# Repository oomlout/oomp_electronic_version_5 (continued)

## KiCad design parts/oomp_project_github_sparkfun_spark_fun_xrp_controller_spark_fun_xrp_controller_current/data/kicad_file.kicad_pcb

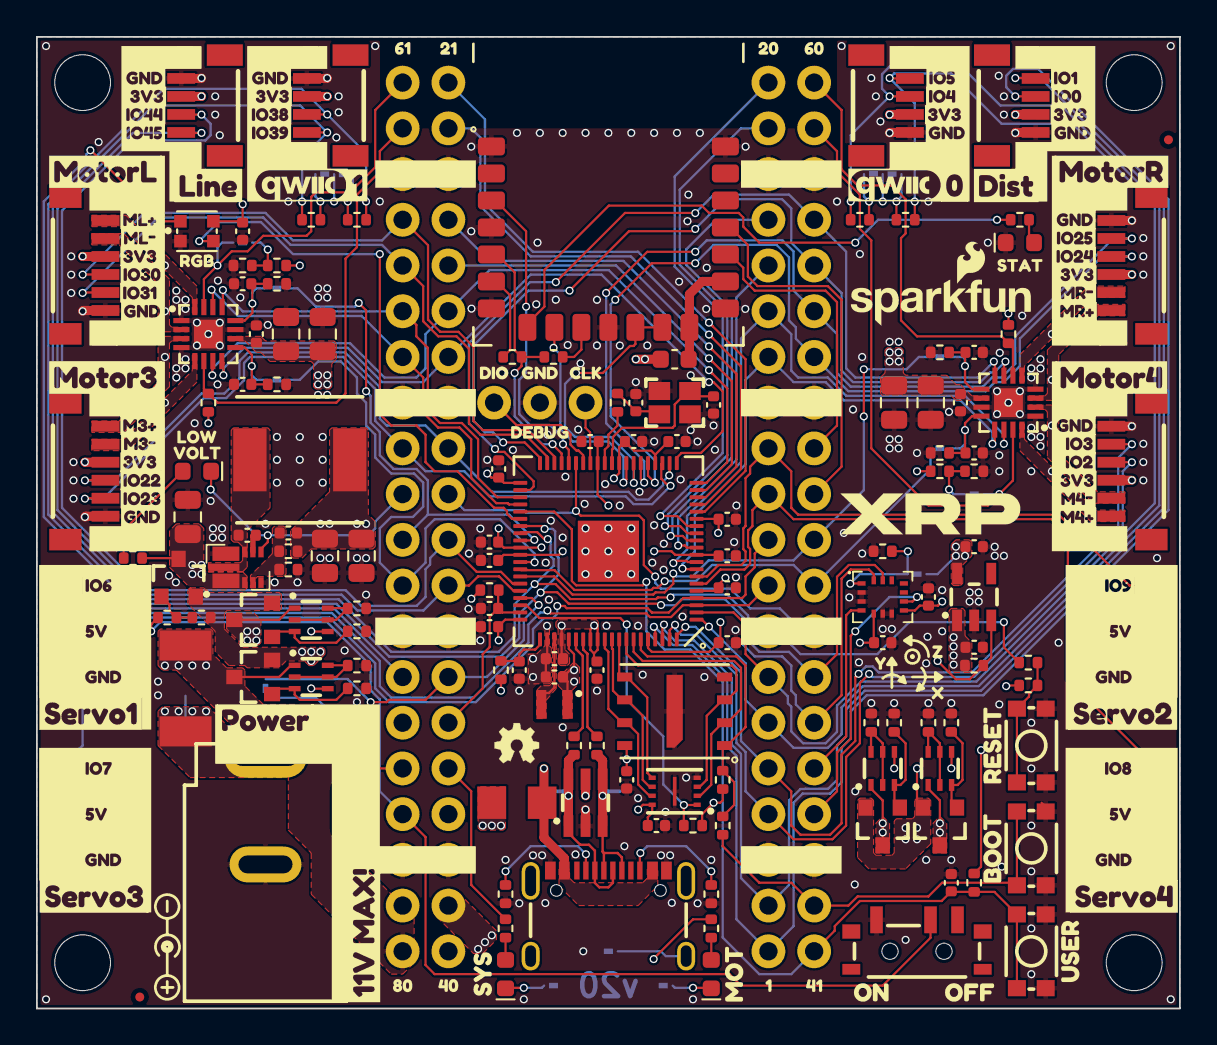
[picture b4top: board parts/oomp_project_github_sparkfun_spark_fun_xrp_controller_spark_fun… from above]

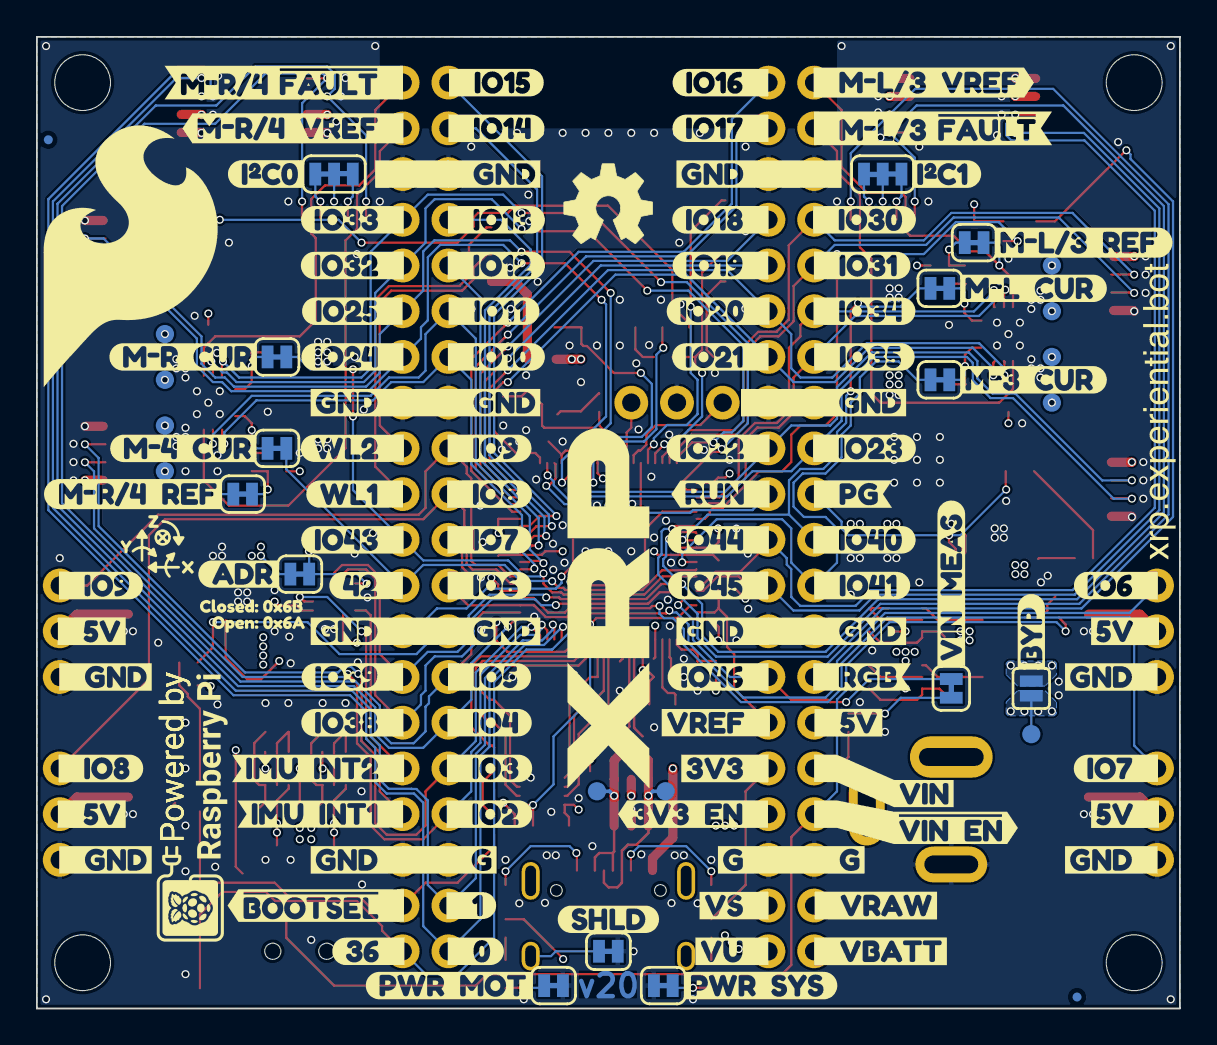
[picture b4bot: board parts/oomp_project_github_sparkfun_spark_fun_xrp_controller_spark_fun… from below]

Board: 6 copper layers, 63.5 x 54.0 mm, 385 parts (137 on the bottom side), 137 nets.

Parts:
C1, C2, C3, C4, C5, C6, C7, C8, C9, C10, C11, C19, C20, C22, C28, C29, C30, C31, C34, C37, C42, C43, C44, C45: 0.1uF; C_0402_1005Metric
C12, C13, C14, C15, C16, C26, C27: 4.7uF; C_0402_1005Metric
C17, C18: 15pF; C_0402_1005Metric
C21, C24, C25, C32, C33, C35, C36, C38, C39, C40, C41: 22uF; C_0805_2012Metric
C23: 47pF; C_0402_1005Metric
D1: Blue; LED_0603_1608Metric_Blue
D2, D3, D6: Red; LED_0603_1608Metric_Red
D4: WS2812B; WS2812_2020
D5: DT1042-04SO; SOT23-6
F1: 16V/2.5A/5.0A; 1812
F2: 6V/0.75A/1.5A; 1206
FID1, FID2, FID3, FID4: Fiducial_0.5mm; Fiducial_0.5mm_Mask1mm
G3: OSHW_Logo; Creative_Commons_License
J1: Barrel_Jack_PTH_Slot; Power_Jack_PTH_Slot
J2: USB_C_Receptacle; USB-C_16
J3, J8, J9, J10, J11: Conn_01x03; 1x03
J4, J5, J6, J7: Conn_01x20; 1x20
J12, J15: JST_SMD_1.0mm_Vertical; JST_SMD_1.0mm-4_Vertical
J13, J14: Qwiic_Vertical; JST_SMD_1.0mm-4_Vertical
J16, J17, J18, J19: Conn_01x06; JST_SMD_1.0mm-6_Vertical
JP1: PWR_SYS; Jumper_2_NC_Trace
JP2: PWR_MOT; Jumper_2_NC_Trace
JP3: BYP; Jumper_2_NO
JP4: ADR; Jumper_2_NC_Trace
JP5: I2C1; Jumper_3_NC-2_Trace
JP6: I2C0; Jumper_3_NC-2_Trace
JP7: SHLD; Jumper_2_NC_Trace
JP8: ML3_REF; Jumper_2_NC_Trace
JP9: MR4_REF; Jumper_2_NC_Trace
JP10: ML_CUR; Jumper_2_NC_Trace
JP11: M3_CUR; Jumper_2_NC_Trace
JP12: M4_CUR; Jumper_2_NC_Trace
JP13: MR_CUR; Jumper_2_NC_Trace
JP14: VIN_MEAS; Jumper_2_NC_Trace
L1: 3.3uH; 0806_Polarized
L2: 6.8uH; Inductor_7.3x6.6mm
L3: 470Ohm; C_0603_1608Metric
Q1, Q3, Q5, Q7: BCM857BS-7-F; SOT-323
Q2, Q4, Q6, Q8, Q9: DMG2305UX; SOT23-3
R1: 200; R_0402_1005Metric
R2: 33; R_0402_1005Metric
R3, R18, R20: 1k; R_0402_1005Metric
R4, R5: 27; R_0402_1005Metric
R6, R7, R12, R41: 10k; R_0402_1005Metric
R8: 180k; R_0402_1005Metric
R9, R23: 33k; R_0402_1005Metric
R10, R14, R15, R16, R17: 2.2k; R_0402_1005Metric
R11, R47: 4.7k; R_0402_1005Metric
R13, R19, R21, R22, R30, R31, R32, R33, R34, R35, R36, R37, R38, R39, R42, R43, R44, R45, R46, R48, R49: 100k; R_0402_1005Metric
R24, R25, R26, R27, R28, R29: 5.1k; R_0402_1005Metric
R40: 470; R_0402_1005Metric
Ref**: Val**; POLARITY_MARKING_CENTER_POSITIVE
Ref**#2: Val**; OSHW_Logo_2.5mm
Ref**#3: Val**; OSHW_Logo_5mm
ST1, ST2, ST3, ST4: Standoff
SW1: SPDT_Slide_SMD_6.7x2.6mm; Slide_SPST_SMD_6.7x2.6mm
SW2: RESET; Push_SMD_4.6x2.8mm_h2.5mm
SW3: BOOT; Push_SMD_4.6x2.8mm_h2.5mm
SW4: USER; Push_SMD_4.6x2.8mm_h2.5mm
TP1, TP2, TP4, TP5, TP6, TP7, TP8, TP9, TP10, TP11, TP12: 1.0mm; TestPoint-1.0mm
U1: RP2350B; QFN-80-1EP_10x10mm_P0.4mm_EP3.4x3.4mm
U2: W25Q128JVPIM; WDFN-8_6x5mm-SkinnyCenterPad
U3: APS6404L-3SQR-ZR; USON-8_3x2mm-SkinnyCenterPad
U4: AP63357DV-7; PowerVFDFN-13
U5: RT9080-3.3; SOT23-5
U6: LSM6DSOX; LGA-14L
U7, U8: DRV8411A; QFN-16
U9: RM2; RM2_Tight
Y1: 12MHz; Crystal_SMD_2.5x2.0mm
kibuzzard-66C8BA89: G***; kibuzzard-66C8BA89
kibuzzard-66C8BABD: G***; kibuzzard-66C8BABD
kibuzzard-66C8BAD7: G***; kibuzzard-66C8BAD7
kibuzzard-66C8BAE0: G***; kibuzzard-66C8BAE0
kibuzzard-66C8BAF9: G***; kibuzzard-66C8BAF9
kibuzzard-66C8BB00: G***; kibuzzard-66C8BB00
kibuzzard-66C8BB0B: G***; kibuzzard-66C8BB0B
kibuzzard-66C8BB07: G***; kibuzzard-66C8BB07
kibuzzard-66C8BB11: G***; kibuzzard-66C8BB11
kibuzzard-66C8BB15: G***; kibuzzard-66C8BB15
kibuzzard-66C8BB40: G***; kibuzzard-66C8BB40
kibuzzard-66C8BC20, kibuzzard-66C8BC20#2, kibuzzard-66C8BC20#3, kibuzzard-66C8BC20#4, kibuzzard-66C8BC20#5, kibuzzard-66C8BC20#6, kibuzzard-66C8BC20#7, kibuzzard-66C8BC20#8, kibuzzard-66C8BC20#9, kibuzzard-66C8BC20#10, kibuzzard-66C8BC20#11, kibuzzard-66C8BC20#12: G***; kibuzzard-66C8BC20
kibuzzard-66C8BCAF: G***; kibuzzard-66C8BCAF
kibuzzard-66C8BCB7: G***; kibuzzard-66C8BCB7
kibuzzard-66C8BCBF, kibuzzard-66C8BCBF#2, kibuzzard-66C8BCBF#3, kibuzzard-66C8BCBF#4, kibuzzard-66C8BCBF#5, kibuzzard-66C8BCBF#6, kibuzzard-66C8BCBF#7, kibuzzard-66C8BCBF#8: G***; kibuzzard-66C8BCBF
kibuzzard-66C8BCC4: G***; kibuzzard-66C8BCC4
kibuzzard-66C8BCCB: G***; kibuzzard-66C8BCCB
kibuzzard-66C8BD65, kibuzzard-66C8BD65#2, kibuzzard-66C8BD65#3, kibuzzard-66C8BD65#4: G***; kibuzzard-66C8BD65
kibuzzard-66C8C0A3: G***; kibuzzard-66C8C0A3
kibuzzard-66C8C0B9: G***; kibuzzard-66C8C0B9
kibuzzard-66C8C028: G***; kibuzzard-66C8C028
kibuzzard-66C8C031: G***; kibuzzard-66C8C031
kibuzzard-66D0C3E9: G***; kibuzzard-66D0C3E9
kibuzzard-66D0C3F4: G***; kibuzzard-66D0C3F4
kibuzzard-66D0F23E: G***; kibuzzard-66D0F23E
kibuzzard-675A0A02: G***; kibuzzard-675A0A02
kibuzzard-675A0A2C: G***; kibuzzard-675A0A2C
kibuzzard-675A0A3A: G***; kibuzzard-675A0A3A
kibuzzard-675A0A4A: G***; kibuzzard-675A0A4A
kibuzzard-675A0A6A: G***; kibuzzard-675A0A6A
kibuzzard-675A0A8E: G***; kibuzzard-675A0A8E
kibuzzard-675A0A9F: G***; kibuzzard-675A0A9F
kibuzzard-675A0A13: G***; kibuzzard-675A0A13
kibuzzard-675A0A24: G***; kibuzzard-675A0A24
kibuzzard-675A0A32: G***; kibuzzard-675A0A32
kibuzzard-675A0A42: G***; kibuzzard-675A0A42
kibuzzard-675A0A51: G***; kibuzzard-675A0A51
kibuzzard-675A0A59: G***; kibuzzard-675A0A59
kibuzzard-675A0A60: G***; kibuzzard-675A0A60
kibuzzard-675A0A71: G***; kibuzzard-675A0A71
kibuzzard-675A0A79: G***; kibuzzard-675A0A79
kibuzzard-675A0A84: G***; kibuzzard-675A0A84
kibuzzard-675A0AA6: G***; kibuzzard-675A0AA6
kibuzzard-675A0B2A: G***; kibuzzard-675A0B2A
kibuzzard-675A0B4B: G***; kibuzzard-675A0B4B
kibuzzard-675A0B42: G***; kibuzzard-675A0B42
kibuzzard-675A0C02: G***; kibuzzard-675A0C02
kibuzzard-675A0C47: G***; kibuzzard-675A0C47
kibuzzard-675A0C69: G***; kibuzzard-675A0C69
kibuzzard-675A0C74: G***; kibuzzard-675A0C74
kibuzzard-675A0CA1: G***; kibuzzard-675A0CA1
kibuzzard-675A07AD: G***; kibuzzard-675A07AD
kibuzzard-675A07C3: G***; kibuzzard-675A07C3
kibuzzard-675A07CE: G***; kibuzzard-675A07CE
kibuzzard-675A07D8: G***; kibuzzard-675A07D8
kibuzzard-675A07E1: G***; kibuzzard-675A07E1
kibuzzard-675A08A3: G***; kibuzzard-675A08A3
kibuzzard-675A08AB: G***; kibuzzard-675A08AB
kibuzzard-675A08B3: G***; kibuzzard-675A08B3
kibuzzard-675A08BE: G***; kibuzzard-675A08BE
kibuzzard-675A08C5: G***; kibuzzard-675A08C5
kibuzzard-675A08CC: G***; kibuzzard-675A08CC
kibuzzard-675A08D1: G***; kibuzzard-675A08D1
kibuzzard-675A08D7: G***; kibuzzard-675A08D7
kibuzzard-675A08DD: G***; kibuzzard-675A08DD
kibuzzard-675A08E8: G***; kibuzzard-675A08E8
kibuzzard-675A08F4: G***; kibuzzard-675A08F4
kibuzzard-675A09A0: G***; kibuzzard-675A09A0
kibuzzard-675A09AB: G***; kibuzzard-675A09AB
kibuzzard-675A09C6: G***; kibuzzard-675A09C6
kibuzzard-675A09D0: G***; kibuzzard-675A09D0
kibuzzard-675A09E0: G***; kibuzzard-675A09E0
kibuzzard-675A09E8: G***; kibuzzard-675A09E8
kibuzzard-675A09F0: G***; kibuzzard-675A09F0
kibuzzard-675A09F8: G***; kibuzzard-675A09F8
kibuzzard-675A081C: G***; kibuzzard-675A081C
kibuzzard-675A082E: G***; kibuzzard-675A082E
kibuzzard-675A086F: G***; kibuzzard-675A086F
kibuzzard-675A089C: G***; kibuzzard-675A089C
kibuzzard-675A090C: G***; kibuzzard-675A090C
kibuzzard-675A094C: G***; kibuzzard-675A094C
kibuzzard-675A099A: G***; kibuzzard-675A099A
kibuzzard-675A0814: G***; kibuzzard-675A0814
kibuzzard-675A0838: G***; kibuzzard-675A0838
kibuzzard-675A0858: G***; kibuzzard-675A0858
kibuzzard-675A0863: G***; kibuzzard-675A0863
kibuzzard-675A0896: G***; kibuzzard-675A0896
kibuzzard-675A0913: G***; kibuzzard-675A0913
kibuzzard-675A0923: G***; kibuzzard-675A0923
kibuzzard-675A0928: G***; kibuzzard-675A0928
kibuzzard-675A0935: G***; kibuzzard-675A0935
kibuzzard-675A0944, kibuzzard-675A0944#2: G***; kibuzzard-675A0944
kibuzzard-675A0955: G***; kibuzzard-675A0955
kibuzzard-675A0971: G***; kibuzzard-675A0971
kibuzzard-675A0986: G***; kibuzzard-675A0986
kibuzzard-675B6FE7: G***; kibuzzard-675B6FE7
kibuzzard-675B6FED: G***; kibuzzard-675B6FED
kibuzzard-675B6FF7: G***; kibuzzard-675B6FF7
kibuzzard-675B6FFD: G***; kibuzzard-675B6FFD
kibuzzard-675B70E2: G***; kibuzzard-675B70E2
kibuzzard-675B70F7: G***; kibuzzard-675B70F7
kibuzzard-675B71AA: G***; kibuzzard-675B71AA
kibuzzard-675B71EB: G***; kibuzzard-675B71EB
kibuzzard-675B71EF: G***; kibuzzard-675B71EF
kibuzzard-675B704C: G***; kibuzzard-675B704C
kibuzzard-675B708F: G***; kibuzzard-675B708F
kibuzzard-675B710B: G***; kibuzzard-675B710B
kibuzzard-675B712F: G***; kibuzzard-675B712F
kibuzzard-675B714E: G***; kibuzzard-675B714E
kibuzzard-675B715F: G***; kibuzzard-675B715F
kibuzzard-675B717F: G***; kibuzzard-675B717F
kibuzzard-675B719D: G***; kibuzzard-675B719D
kibuzzard-675B720C: G***; kibuzzard-675B720C
kibuzzard-675B7098: G***; kibuzzard-675B7098
kibuzzard-675B7119: G***; kibuzzard-675B7119
kibuzzard-675B7135: G***; kibuzzard-675B7135
kibuzzard-675B7148: G***; kibuzzard-675B7148
kibuzzard-675B7162: G***; kibuzzard-675B7162
kibuzzard-675B7188: G***; kibuzzard-675B7188
kibuzzard-675B7211: G***; kibuzzard-675B7211
kibuzzard-6705AB8E: G***; kibuzzard-6705AB8E
kibuzzard-6705AB93: G***; kibuzzard-6705AB93
kibuzzard-6705B68C: G***; kibuzzard-6705B68C
kibuzzard-6705B272: G***; kibuzzard-6705B272
kibuzzard-6705B285: G***; kibuzzard-6705B285
kibuzzard-6705B300: G***; kibuzzard-6705B300
kibuzzard-6705B693: G***; kibuzzard-6705B693
kibuzzard-6705B917, kibuzzard-6705B917#2: G***; kibuzzard-6705B917
kibuzzard-6705B921, kibuzzard-6705B921#2: G***; kibuzzard-6705B921
kibuzzard-6705B925, kibuzzard-6705B925#2: G***; kibuzzard-6705B925
kibuzzard-6761A9ED: G***; kibuzzard-6761A9ED
kibuzzard-6761A9F2: G***; kibuzzard-6761A9F2
kibuzzard-6761DAD5: G***; kibuzzard-6761DAD5
kibuzzard-6761DADD: G***; kibuzzard-6761DADD
kibuzzard-6761DAE0: G***; kibuzzard-6761DAE0
kibuzzard-6761DAE7: G***; kibuzzard-6761DAE7
kibuzzard-6761DAF0: G***; kibuzzard-6761DAF0
kibuzzard-6761DAF5: G***; kibuzzard-6761DAF5
kibuzzard-6761DAFA: G***; kibuzzard-6761DAFA
kibuzzard-6761DB01: G***; kibuzzard-6761DB01
kibuzzard-67057BD8: G***; kibuzzard-67057BD8
kibuzzard-67057BDE: G***; kibuzzard-67057BDE
kibuzzard-67057BE2: G***; kibuzzard-67057BE2
kibuzzard-67630A6A: G***; kibuzzard-67630A6A
kibuzzard-67633F57: G***; kibuzzard-67633F57
kibuzzard-67633FA4: G***; kibuzzard-67633FA4
kibuzzard-67633FC9: G***; kibuzzard-67633FC9
kibuzzard-67633FF0: G***; kibuzzard-67633FF0
kibuzzard-670445F0: G***; kibuzzard-670445F0
kibuzzard-670445F5: G***; kibuzzard-670445F5
kibuzzard-670557F8: G***; kibuzzard-670557F8
kibuzzard-676332CE: G***; kibuzzard-676332CE
kibuzzard-676332E9: G***; kibuzzard-676332E9
kibuzzard-676333FD: G***; kibuzzard-676333FD
kibuzzard-676335B4: G***; kibuzzard-676335B4
kibuzzard-676335CA: G***; kibuzzard-676335CA
kibuzzard-6763323B: G***; kibuzzard-6763323B
kibuzzard-6763343E: G***; kibuzzard-6763343E
kibuzzard-6763344C: G***; kibuzzard-6763344C
kibuzzard-6763351F: G***; kibuzzard-6763351F
kibuzzard-6763356E: G***; kibuzzard-6763356E
kibuzzard-6763576D: G***; kibuzzard-6763576D
kibuzzard-67044314: G***; kibuzzard-67044314
kibuzzard-67044318: G***; kibuzzard-67044318
kibuzzard-67044344: G***; kibuzzard-67044344
kibuzzard-67044349: G***; kibuzzard-67044349
kibuzzard-67044603: G***; kibuzzard-67044603
kibuzzard-67044609: G***; kibuzzard-67044609
kibuzzard-67044610: G***; kibuzzard-67044610
kibuzzard-67044615: G***; kibuzzard-67044615
kibuzzard-67633223: G***; kibuzzard-67633223
kibuzzard-67633419: G***; kibuzzard-67633419
kibuzzard-67633423: G***; kibuzzard-67633423
kibuzzard-67633438: G***; kibuzzard-67633438
kibuzzard-67633519: G***; kibuzzard-67633519
kibuzzard-67633561: G***; kibuzzard-67633561

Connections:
1.1V: C10.1, C11.1, C12.1, C16.1, L1.1, U1.10 (DVDD), U1.32 (DVDD), U1.51 (DVDD), U1.65 (VREG_FB)
3.3V: C1.1, C2.1, C3.1, C4.1, C5.1, C6.1, C7.1, C8.1, C9.1, C15.1, C19.1, C20.1, C27.1, C28.1, C29.1, C30.1, D4.4 (VDD), J6.5, J12.2, J13.2, J14.2, J15.2, J16.3, J17.3, J18.3, J19.3, JP4.2 (B), JP5.2 (B), JP6.2 (B), L3.1, R1.2, R2.2, R6.2, R7.2, R11.2, R19.2, R21.2, R42.2, R44.2, R48.1, R49.1, U1.5 (IOVDD), U1.15 (IOVDD), U1.24 (IOVDD), U1.29 (IOVDD), U1.41 (IOVDD), U1.50 (IOVDD), U1.60 (IOVDD), U1.64 (VREG_VIN), U1.68 (USB_OTP_VDD), U1.69 (QSPI_IOVDD), U1.76 (IOVDD), U2.8 (VCC), U3.8 (VCC), U5.5 (VOUT), U6.5 (VDDIO), U6.8 (VDD)
3V3_EN: J6.4, R46.2, U5.3 (EN)
5V: C23.1, C24.1, C25.1, C38.1, C39.1, C40.1, C41.1, J7.6, J8.2, J9.2, J10.2, J11.2, L2.2, Q7.1 (E), Q8.3 (D), R8.2, R12.2
ADC_VREF: C13.1, J6.6, R1.1, U1.59 (ADC_AVDD)
FLASH_~CS: R6.1, R20.2, U1.75 (QSPI_~CS), U2.1 (~CS)
GND: C1.2, C2.2, C3.2, C4.2, C5.2, C6.2, C7.2, C8.2, C9.2, C10.2, C11.2, C12.2, C13.2, C14.2, C15.2, C16.2, C17.2, C18.2, C19.2, C20.2, C21.2, C24.2, C25.2, C26.2, C27.2, C28.2, C29.2, C30.2, C31.2, C32.2, C33.2, C34.2, C35.2, C36.2, C37.2, C38.2, C39.2, C40.2, C41.2, C42.2, C43.2, C44.2, C45.2, D1.1 (K), D4.2 (VSS), D5.2 (GND), J1.GND, J2.GND, J3.2, J4.3, J4.8, J4.13, J4.18, J5.3, J5.8, J5.13, J5.18, J6.3, J6.8, J6.13, J6.18, J7.3, J7.8, J7.13, J7.18, J8.1, J9.1, J10.1, J11.1, J12.1, J13.1, J14.1, J15.1, J16.6, J17.6, J18.6, J19.6, JP1.1 (A), JP2.1 (A), JP7.2 (B), R9.1, R13.1, R23.1, R24.1, R25.1, R26.1, R27.1, R28.1, R29.1, R30.1, R31.1, R32.1, R33.1, R34.1, R35.1, R36.1, R37.1, R43.1, R45.1, SW1.3 (C), SW2.1, SW3.1, SW4.1, U1.62 (VREG_PGND), U1.EP (GND), U2.4 (GND), U2.EPAD (GND), U3.4 (GND), U3.9 (GND), U4.4 (COMP), U4.8 (GND), U5.2 (GND), U6.2 (SDx), U6.3 (SCx), U6.6 (GND), U6.7 (GND), U7.1 (PGNDA), U7.4 (PGNDB), U7.11 (GND), U7.EP (PAD), U8.1 (PGNDA), U8.4 (PGNDB), U8.11 (GND), U8.EP (PAD), U9.A1 (GND), U9.A4 (GND), U9.A7 (GND), U9.B4 (GND), U9.C1 (GND), U9.C7 (GND), Y1.2, Y1.4
GPIO0/DIST_TRIG: J5.1, J15.3, U1.77 (GPIO0)
GPIO1/DIST_ECHO: J5.2, J15.4, U1.78 (GPIO1)
GPIO2/ENCODER_4A: J5.4, J19.4, U1.79 (GPIO2)
GPIO3/ENCODER_4B: J5.5, J19.5, U1.80 (GPIO3)
GPIO4/SDA0: J5.6, J14.3, R16.1, U1.1 (GPIO4)
GPIO5/SCL0: J5.7, J14.4, R17.2, U1.2 (GPIO5)
GPIO6/SERVO_1: J5.9, J8.3, U1.3 (GPIO6)
GPIO7/SERVO_3: J5.10, J10.3, U1.4 (GPIO7)
GPIO8/SERVO_4: J5.11, J11.3, U1.6 (GPIO8)
GPIO9/SERVO_2: J5.12, J9.3, U1.7 (GPIO9)
GPIO10/MOTOR_4_IN1: J5.14, U1.8 (GPIO10), U8.13 (AIN2)
GPIO11/MOTOR_4_IN2: J5.15, U1.9 (GPIO11), U8.14 (AIN1)
GPIO12: J5.16, U1.11 (GPIO12)
GPIO13: J5.17, U1.12 (GPIO13)
GPIO14: J5.19, U1.13 (GPIO14)
GPIO15: J5.20, U1.14 (GPIO15)
GPIO16: J6.20, U1.16 (GPIO16)
GPIO17: J6.19, U1.17 (GPIO17)
GPIO18: J6.17, U1.18 (GPIO18)
GPIO19: J6.16, U1.19 (GPIO19)
GPIO20/MOTOR_3_IN1: J6.15, U1.20 (GPIO20), U7.7 (BIN1)
GPIO21/MOTOR_3_IN2: J6.14, U1.21 (GPIO21), U7.8 (BIN2)
GPIO22/ENCODER_3A: J6.12, J17.4, U1.22 (GPIO22)
GPIO23/ENCODER_3B: J7.12, J17.5, U1.23 (GPIO23)
GPIO24/ENCODER_RA: J4.14, J18.4, U1.25 (GPIO24)
GPIO25/ENCODER_RB: J4.15, J18.5, U1.26 (GPIO25)
GPIO26/RADIO_ON: U1.27 (GPIO26), U9.B5 (WLON), U9.B6 (BTON)
GPIO27/RADIO_~CS: U1.28 (GPIO27), U9.B2 (~CS)
GPIO28/RADIO_CLK: U1.36 (GPIO28), U9.A3 (SCLK)
GPIO29/RADIO_D: R40.2, R41.2, U1.37 (GPIO29), U9.A5 (PICO)
GPIO30/ENCODER_LA: J7.17, J16.4, U1.38 (GPIO30)
GPIO31/ENCODER_LB: J7.16, J16.5, U1.39 (GPIO31)
GPIO32/MOTOR_R_IN1: J4.16, U1.40 (GPIO32), U8.7 (BIN1)
GPIO33/MOTOR_R_IN2: J4.17, U1.42 (GPIO33), U8.8 (BIN2)
GPIO34/MOTOR_L_IN1: J7.15, U1.43 (GPIO34), U7.13 (AIN2)
GPIO35/MOTOR_L_IN2: J7.14, U1.44 (GPIO35), U7.14 (AIN1)
GPIO36/USER_BUTTON: C31.1, J4.1, R21.1, SW4.2, U1.45 (GPIO36)
GPIO37/NEOPIXEL: D4.3 (DIN), U1.46 (GPIO37)
GPIO38/SDA1: J4.6, J13.3, R14.1, U1.47 (GPIO38), U6.14 (SDA)
GPIO39/SCL1: J4.7, J13.4, R15.2, U1.48 (GPIO39), U6.13 (SCL)
GPIO40/CURRENT_ML: J7.10, JP10.2 (B), U1.49 (ADC0/GPIO40)
GPIO41/CURRENT_M3: J7.9, JP11.2 (B), U1.52 (ADC1/GPIO41)
GPIO42/CURRENT_M4: J4.9, JP12.2 (B), U1.53 (ADC2/GPIO42)
GPIO43/CURRENT_MR: J4.10, JP13.2 (B), U1.54 (ADC3/GPIO43)
GPIO44/LINE_L: J6.10, J12.3, U1.55 (ADC4/GPIO44)
GPIO45/LINE_R: J6.9, J12.4, U1.56 (ADC5/GPIO45)
GPIO46/VIN_MEAS: J6.7, JP14.2 (B), U1.57 (ADC6/GPIO46)
GPIO47/PSRAM_~CS: R7.1, U1.58 (ADC7/GPIO47), U3.1 (~CS)
IMU_INT1: J4.5, U6.4 (INT1)
IMU_INT2: J4.4, U6.9 (INT2)
MOTOR_3_OUT+: J17.1, TP8.1, U7.3 (BOUT2)
MOTOR_3_OUT-: J17.2, TP7.1, U7.5 (BOUT1)
MOTOR_4_OUT+: J19.1, TP9.1, U8.16 (AOUT1)
MOTOR_4_OUT-: J19.2, TP10.1, U8.2 (AOUT2)
MOTOR_L_OUT+: J16.1, TP5.1, U7.16 (AOUT1)
MOTOR_L_OUT-: J16.2, TP6.1, U7.2 (AOUT2)
MOTOR_L/3_VREF: J7.20, JP8.2 (B), U7.15 (VREF)
MOTOR_L/3_~FAULT: J7.19, R48.2, U7.6 (~FAULT)
MOTOR_R_OUT+: J18.1, TP12.1, U8.3 (BOUT2)
MOTOR_R_OUT-: J18.2, TP11.1, U8.5 (BOUT1)
MOTOR_R/4_VREF: J4.19, JP9.2 (B), U8.15 (VREF)
MOTOR_R/4_~FAULT: J4.20, R49.2, U8.6 (~FAULT)
NEOPIXEL_OUT: D4.1 (DOUT), J7.7
unnamed: C18.1, R3.1, Y1.3
unnamed: D1.2 (A), R10.1
unnamed: D2.2 (A), R11.1
unnamed: D2.1 (K), JP1.2 (B)
unnamed: D3.2 (A), R12.1
unnamed: D3.1 (K), JP2.2 (B)
unnamed: D5.5 (VCC), F2.1, J2.VBUS
unnamed: D6.2 (A), R47.1
unnamed: J2.A5 (CC1), R29.2
unnamed: J2.B5 (CC2), R28.2
unnamed: J2.S (SHIELD), JP7.1 (A)
unnamed: F1.1, J1.PWR, JP3.1 (A), TP4.1
unnamed: JP4.1 (A), R13.2, U6.1 (SDO/SA0)
unnamed: JP5.1 (A), R15.1
unnamed: JP5.3 (C), R14.2
unnamed: JP6.1 (A), R17.1
unnamed: JP6.3 (C), R16.2
unnamed: JP8.1 (A), R42.1, R43.2
unnamed: JP9.1 (A), R44.1, R45.2
unnamed: C42.1, JP10.1 (A), R24.2, U7.12 (AIPROPI)
unnamed: C43.1, JP11.1 (A), R25.2, U7.9 (BIPROPI)
unnamed: C44.1, JP12.1 (A), R26.2, U8.12 (AIPROPI)
unnamed: C45.1, JP13.1 (A), R27.2, U8.9 (BIPROPI)
unnamed: JP14.1 (A), R22.1, R23.2
unnamed: Q1.2 (B), Q1.5 (B), Q1.6 (C), R30.2
unnamed: Q1.3 (C), Q2.1 (G), R31.2
unnamed: Q3.2 (B), Q3.5 (B), Q3.6 (C), R32.2
unnamed: Q3.3 (C), Q4.1 (G), R33.2
unnamed: Q5.2 (B), Q5.5 (B), Q5.6 (C), R34.2
unnamed: Q5.3 (C), Q6.1 (G), R35.2
unnamed: Q7.2 (B), Q7.5 (B), Q7.6 (C), R36.2
unnamed: Q7.3 (C), Q8.1 (G), R37.2
unnamed: Q9.1 (G), R38.1, R39.2
unnamed: R18.1, R19.1, SW2.2
unnamed: C14.1, R2.1, U1.61 (VREG_AVDD)
unnamed: L1.2, U1.63 (VREG_LX)
unnamed: C17.1, U1.30 (XIN), Y1.1
unnamed: R3.2, U1.31 (XOUT)
unnamed: C22.1, U4.6 (BST)
unnamed: C23.2, R8.1, R9.2, U4.3 (FB)
unnamed: C22.2, L2.1, U4.7 (NC), U4.9 (SW)
unnamed: R41.1, U9.B3 (IRQ)
unnamed: R40.1, U9.A6 (POCI)
unnamed: L3.2, U9.B7 (VDDIO), U9.C2 (VDDBAT)
POWER_GOOD: D6.1 (K), J7.11, U4.5 (PG)
QSPI_CLK: U1.71 (QSPI_SCLK), U2.6 (CLK), U3.6 (CLK)
QSPI_D0: U1.72 (QSPI_SD0), U2.5 (D0/DI), U3.5 (D0/DI)
QSPI_D1: U1.74 (QSPI_SD1), U2.2 (D1/DO), U3.2 (D1/DO)
QSPI_D2: U1.73 (QSPI_SD2), U2.3 (D2/~WP), U3.3 (D2/~WP)
QSPI_D3: U1.70 (QSPI_SD3), U2.7 (D3/~HOLD), U3.7 (D3/~HOLD)
RADIO_GPIO0/LED: R10.2, U9.B1 (GPIO0)
RADIO_GPIO1: J4.11, U9.C4 (GPIO1)
RADIO_GPIO2: J4.12, U9.C3 (GPIO2)
RUN: J6.11, R18.2, U1.35 (RUN)
SWDCLK: J3.1, U1.33 (SWCLK)
SWDIO: J3.3, U1.34 (SWDIO)
USB_D+: D5.3 (I/O2), D5.4 (I/O3), J2.A6 (D+), J2.B6 (D+), R4.2, TP1.1
USB_D-: D5.1 (I/O1), D5.6 (I/O4), J2.A7 (D-), J2.B7 (D-), R5.1, TP2.1
USB_RP_D+: R4.1, U1.67 (USB_D+)
USB_RP_D-: R5.2, U1.66 (USB_D-)
VBATT: F1.2, J7.1, JP3.2 (B), Q1.1 (E), Q2.3 (D)
VIN: C21.1, C32.1, C33.1, C34.1, C35.1, C36.1, C37.1, J7.5, Q9.3 (D), R22.2, R47.2, U4.1 (VIN), U4.2 (EN), U7.10 (VM), U8.10 (VM)
VRAW: J7.2, Q1.4 (E), Q2.2 (S), Q3.4 (E), Q4.2 (S), Q9.2 (S), R38.2
VSYS: C26.1, J6.2, Q5.4 (E), Q6.2 (S), Q7.4 (E), Q8.2 (S), R46.1, U5.1 (VIN)
VUSB: F2.2, J6.1, Q3.1 (E), Q4.3 (D), Q5.1 (E), Q6.3 (D)
~BOOTSEL: J4.2, R20.1, SW3.2
~VIN_EN: J7.4, R39.1, SW1.2
